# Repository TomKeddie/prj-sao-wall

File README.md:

# prj-sao-wall

## Nov2020 Errata
- Untested

## Sep2020 Errata
- add jtag pins
- SPI header has rows swapped and wierd footprint
- Connectors on either end are too close to the edge
- xtal footprint is wrong (need 4 pin)
- C8 move to Y centre to narrow slot width
- X3 change to power pwm
- change to 500mA pnp transistors in place of n-fets
- change to 4x2 connectors on either end

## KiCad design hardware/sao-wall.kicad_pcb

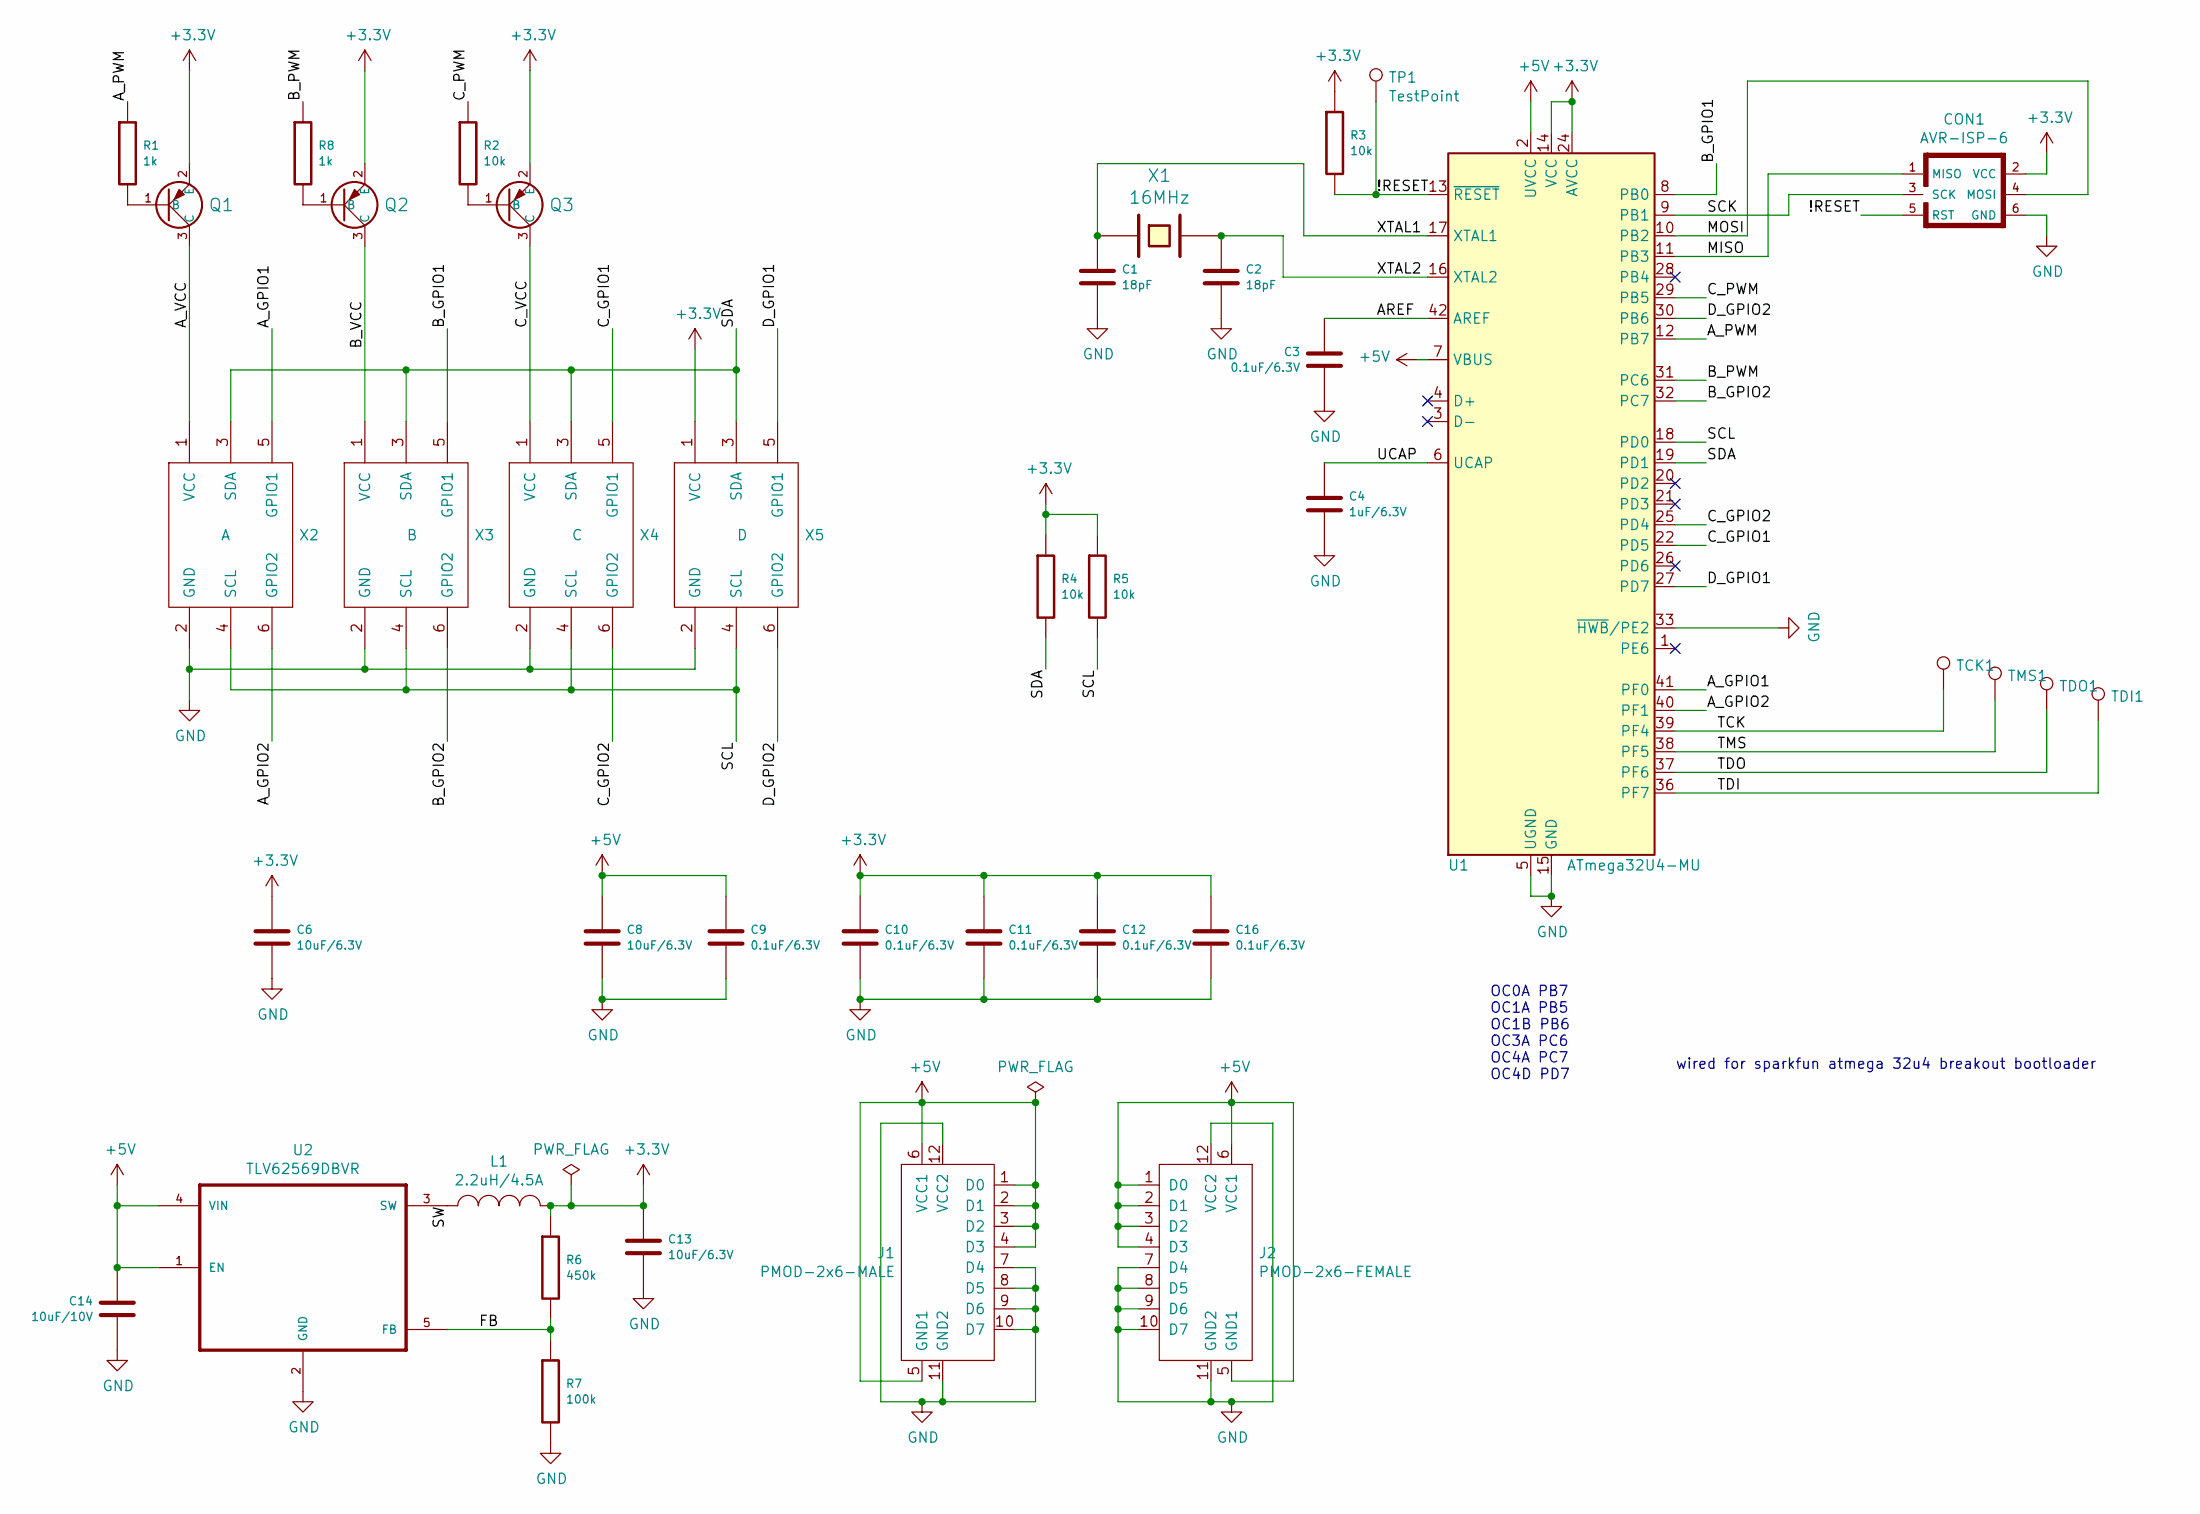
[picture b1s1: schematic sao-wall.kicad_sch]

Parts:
C1, C2: 18pF; C_0805_2012Metric
C3, C9, C10, C11, C12, C16: 0.1uF/6.3V; C_0805_2012Metric
C4: 1uF/6.3V; C_0805_2012Metric
C6, C8, C13: 10uF/6.3V; C_0805_2012Metric
C14: 10uF/10V; C_0805_2012Metric
CON1: AVR-ISP-6; PinTestpoint_2x03_P2.54mm_Vertical
J1: PMOD-2x6-MALE; 2X6_SMD_RA_PLUG
J2: PMOD-2x6-FEMALE; 2X6_SMD_RA_SOCKET
L1: 2.2uH/4.5A; L_MWSA0518S
Q1, Q2, Q3: PMBT2907A_PNP_500mA; SOT23_NXP
R1, R8: 1k; R_0805_2012Metric
R2, R3, R4, R5: 10k; R_0805_2012Metric
R6: 450k; R_0805_2012Metric
R7: 100k; R_0805_2012Metric
TCK1: TCK; TestPoint_Pad_D1.5mm
TDI1: TDI; TestPoint_Pad_D1.5mm
TDO1: TDO; TestPoint_Pad_D1.5mm
TMS1: TMS; TestPoint_Pad_D1.5mm
TP1: TestPoint; TestPoint_Pad_D1.5mm
U1: ATmega32U4-MU; TQFP-44_10x10mm_P0.8mm
U2: TLV62569DBVR; SOT-23-5; LCSC C141836
X1: 16MHz; Crystal_SMD_5032-2Pin_5.0x3.2mm; MPN CX5032GB16
X2: A; Badgelife-SAOv169-SAO-2x3
X3: B; Badgelife-SAOv169-SAO-2x3
X4: C; Badgelife-SAOv169-SAO-2x3
X5: D; Badgelife-SAOv169-SAO-2x3

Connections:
+3.3V: C6.1, C10.1, C11.1, C12.1, C13.1, C16.1, CON1.2 (VCC), L1.2, Q1.2 (E), Q2.2 (E), Q3.2 (E), R3.1, R4.1, R5.1, R6.1, U1.14 (VCC), U1.24 (AVCC), U1.34 (VCC), U1.44 (AVCC), X5.1 (VCC)
+5V: C8.1, C9.1, C14.2, J1.1 (D0), J1.2 (D1), J1.3 (D2), J1.4 (D3), J1.5 (GND1), J1.6 (VCC1), J2.1 (D0), J2.2 (D1), J2.3 (D2), J2.4 (D3), J2.5 (GND1), J2.6 (VCC1), U1.2 (UVCC), U1.7 (VBUS), U2.1 (EN), U2.4 (VIN)
/!RESET: CON1.5 (RST), R3.2, TP1.1, U1.13 (~RESET)
/AREF: C3.2, U1.42 (AREF)
/A_GPIO1: U1.41 (PF0), X2.5 (GPIO1)
/A_GPIO2: U1.40 (PF1), X2.6 (GPIO2)
/A_PWM: R1.1, U1.12 (PB7)
/A_VCC: Q1.3 (C), X2.1 (VCC)
/B_GPIO1: U1.8 (PB0), X3.5 (GPIO1)
/B_GPIO2: U1.32 (PC7), X3.6 (GPIO2)
/B_PWM: R8.1, U1.31 (PC6)
/B_VCC: Q2.3 (C), X3.1 (VCC)
/C_GPIO1: U1.22 (PD5), X4.5 (GPIO1)
/C_GPIO2: U1.25 (PD4), X4.6 (GPIO2)
/C_PWM: R2.1, U1.29 (PB5)
/C_VCC: Q3.3 (C), X4.1 (VCC)
/D_GPIO1: U1.27 (PD7), X5.5 (GPIO1)
/D_GPIO2: U1.30 (PB6), X5.6 (GPIO2)
/FB: R6.2, R7.1, U2.5 (FB)
/MISO: CON1.1 (MISO), U1.11 (PB3)
/MOSI: CON1.4 (MOSI), U1.10 (PB2)
/SCK: CON1.3 (SCK), U1.9 (PB1)
/SCL: R5.2, U1.18 (PD0), X2.4 (SCL), X3.4 (SCL), X4.4 (SCL), X5.4 (SCL)
/SDA: R4.2, U1.19 (PD1), X2.3 (SDA), X3.3 (SDA), X4.3 (SDA), X5.3 (SDA)
/SW: L1.1, U2.3 (SW)
/TCK: TCK1.1, U1.39 (PF4)
/TDI: TDI1.1, U1.36 (PF7)
/TDO: TDO1.1, U1.37 (PF6)
/TMS: TMS1.1, U1.38 (PF5)
/UCAP: C4.1, U1.6 (UCAP)
/XTAL1: C1.1, U1.17 (XTAL1), X1.1
/XTAL2: C2.1, U1.16 (XTAL2), X1.2
GND: C1.2, C2.2, C3.1, C4.2, C6.2, C8.2, C9.2, C10.2, C11.2, C12.2, C13.2, C14.1, C16.2, CON1.6 (GND), J1.7 (D4), J1.8 (D5), J1.9 (D6), J1.10 (D7), J1.11 (GND2), J1.12 (VCC2), J2.7 (D4), J2.8 (D5), J2.9 (D6), J2.10 (D7), J2.11 (GND2), J2.12 (VCC2), R7.2, U1.5 (UGND), U1.15 (GND), U1.23 (GND), U1.33 (~HWB/PE2), U1.35 (GND), U1.43 (GND), U1.45 (GND), U2.2 (GND), X2.2 (GND), X3.2 (GND), X4.2 (GND), X5.2 (GND)
unnamed: Q1.1 (B), R1.2
unnamed: Q2.1 (B), R8.2
unnamed: Q3.1 (B), R2.2

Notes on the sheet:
wired for sparkfun atmega 32u4 breakout bootloader
OC0A PB7 OC1A PB5 OC1B PB6 OC3A PC6 OC4A PC7 OC4D PD7

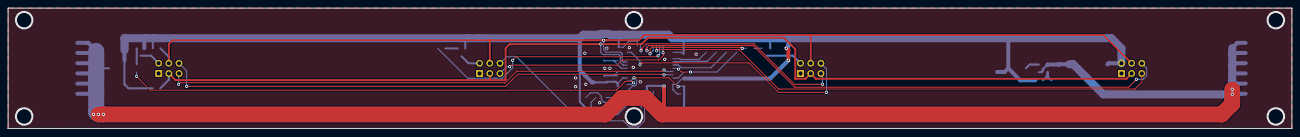
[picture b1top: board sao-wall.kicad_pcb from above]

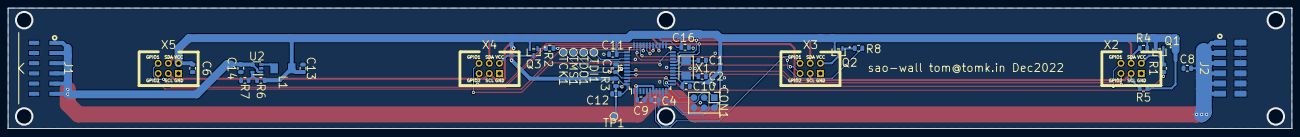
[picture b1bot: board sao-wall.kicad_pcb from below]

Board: 2 copper layers, 320.0 x 30.0 mm, 40 parts (36 on the bottom side), 36 nets.

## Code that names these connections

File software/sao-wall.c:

#include <stdlib.h>
#include <avr/io.h>
#include <avr/interrupt.h>

// Pins
// A_PWM   OC0A PB7 (Arduino D11)
// B_PWM   OC3A PC6 (Arduino D5)
// C_PWM   OC1A PB5 (Arduino D9)
// D_GPIO2 OC1B PB6 (Arduino D10)
// D_GPIO1 OC4D PD7 (Arduino D6)

#define A_GPIO1 PF0
#define A_GPIO2 PF1
#define C_GPIO1 PF4
#define C_GPIO2 PF5

static volatile uint8_t m_level0 = 4+0*256/5;
static volatile uint8_t m_level1 = 4+1*256/5;
static volatile uint8_t m_level2 = 4+2*256/5;
static volatile uint8_t m_level3 = 4+3*256/5;
static volatile uint8_t m_level4 = 4+4*256/5;


static void update_ocr(void) {
    OCR0A = m_level0;
    OCR3A = m_level1;
    OCR1A = m_level2;
    OCR1B = m_level3;
    OCR4D = m_level4;
}    

void main(void) {
    DDRB = (1 << DDB5) | (1 << DDB6) | (1 << DDB7);
    DDRC = (1 << DDC6);
    DDRD = (1 << DDD7) | (1 << DDD1);
    DDRF = (1 << DDF5) | (1 << DDF4) | (1 << DDF1) | (1 << DDF0);

    // use timer 0 to drive the level change logic
    TIFR0  = 0;
    TIMSK0 = (1 << TOIE0);
    
    TCCR0A = (1 << WGM00) | (1 << COM0A0) | (1 << COM0A1); // 8 bit, non inverting on A
    TCCR0B = (1 << CS02); // Set up timer as /256 (16000000 / 256) = 62500 Hz / 512 = 122 Hz
    TCCR1A = (1 << WGM10) | (1 << COM1A1) | (1 << COM1A0) | (1 << COM1B1) | (1 << COM1B0); // 8 bit, non-inverting on A and B
    TCCR1B = (1 << CS12); // Set up timer as /256 (16000000 / 256) = 62500 Hz / 512 = 122 Hz
    TCCR3A = (1 << WGM30) | (1 << COM3A0) | (1 << COM3A1); // 8 bit, non inverting on A
    TCCR3B = (1 << CS32); // Set up timer as /256 (16000000 / 256) = 62500 Hz / 512 = 122 Hz
    TCCR4A = (1 << PWM4A) | (1 << COM4A0) | (1 << COM4A1); // 8 bit, non inverting on A
    TCCR4B = (1 << CS43) | (1 << CS40); // Set up timer as /256 (16000000 / 256) = 62500 Hz / 512 = 122 Hz
    TCCR4C = (1 << COM4A1S) | (1 << COM4A0S) | (1 << PWM4D) | (1 << COM4D0) | (1 << COM4D1); // 8 bit, non inverting on D
    TCCR4D = (1 << WGM40); // phase/freq correct

    sei();

    PORTF |= 1;
    PORTF &= !1;

    PORTF |= 1;
    PORTF &= !1;

    update_ocr();

    while(1) {} ;
}

ISR(TIMER0_OVF_vect) {
    static uint8_t counter = 0;
    static uint8_t increment0 = 1;
    static uint8_t increment1 = 1;
    static uint8_t increment2 = 1;
    static uint8_t increment3 = 1;
    static uint8_t increment4 = 1;
    if (++counter == 8) {
        counter = 0;
        if (increment0) m_level0++; else m_level0--;
        if (increment1) m_level1++; else m_level1--;
        if (increment2) m_level2++; else m_level2--;
        if (increment3) m_level3++; else m_level3--;
        if (increment4) m_level4++; else m_level4--;
        if (m_level0 == 0xff) increment0 = 0; if (m_level0 == 4) increment0 = 1;
        if (m_level1 == 0xff) increment1 = 0; if (m_level1 == 4) increment1 = 1;
        if (m_level2 == 0xff) increment2 = 0; if (m_level2 == 4) increment2 = 1;
        if (m_level3 == 0xff) increment3 = 0; if (m_level3 == 4) increment3 = 1;
        if (m_level4 == 0xff) increment4 = 0; if (m_level4 == 4) increment4 = 1;
        update_ocr();
    }
}

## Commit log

2020-09-29 sao-wall : as sent to jlcpcb Sep 2020
2020-10-07 software: OC0A, OC1A and OC1B working at 122Hz
2020-10-07 software: config for all 6 pwm channels, OC4A seems not to be working
2020-10-09 Software: All 6 channels of pwm working at different rates, added COM4A1S & COM4A0S
2020-10-10 software: working but CRT is hacked in
2020-10-10 software: remove explicit crt and add correct mcu definition
2020-10-10 software: all channel pulsing but not at the right pattern
2020-10-10 Getting pcb design ready to move to separate repo
2020-10-10 software: added 5 more counters, works
2020-10-10 Added pcb files from prj-pcb-experiments
2020-10-10 Added badgelife-parts repo as submodule
2020-10-30 Update readme with Sep 2020 errata
2020-10-30 software: change to 5 channels, sweep full 8 bit range
2020-11-02 hardware: Nov2020 version of pcb with errata fixed
2022-12-23 hardware: update files to kicad 6
2022-12-24 hardware: move to QFP cpu package, Dec2022 release

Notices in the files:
parts and their libraries:
Copyright 2016 Accelerated Designs. All rights reserved.
